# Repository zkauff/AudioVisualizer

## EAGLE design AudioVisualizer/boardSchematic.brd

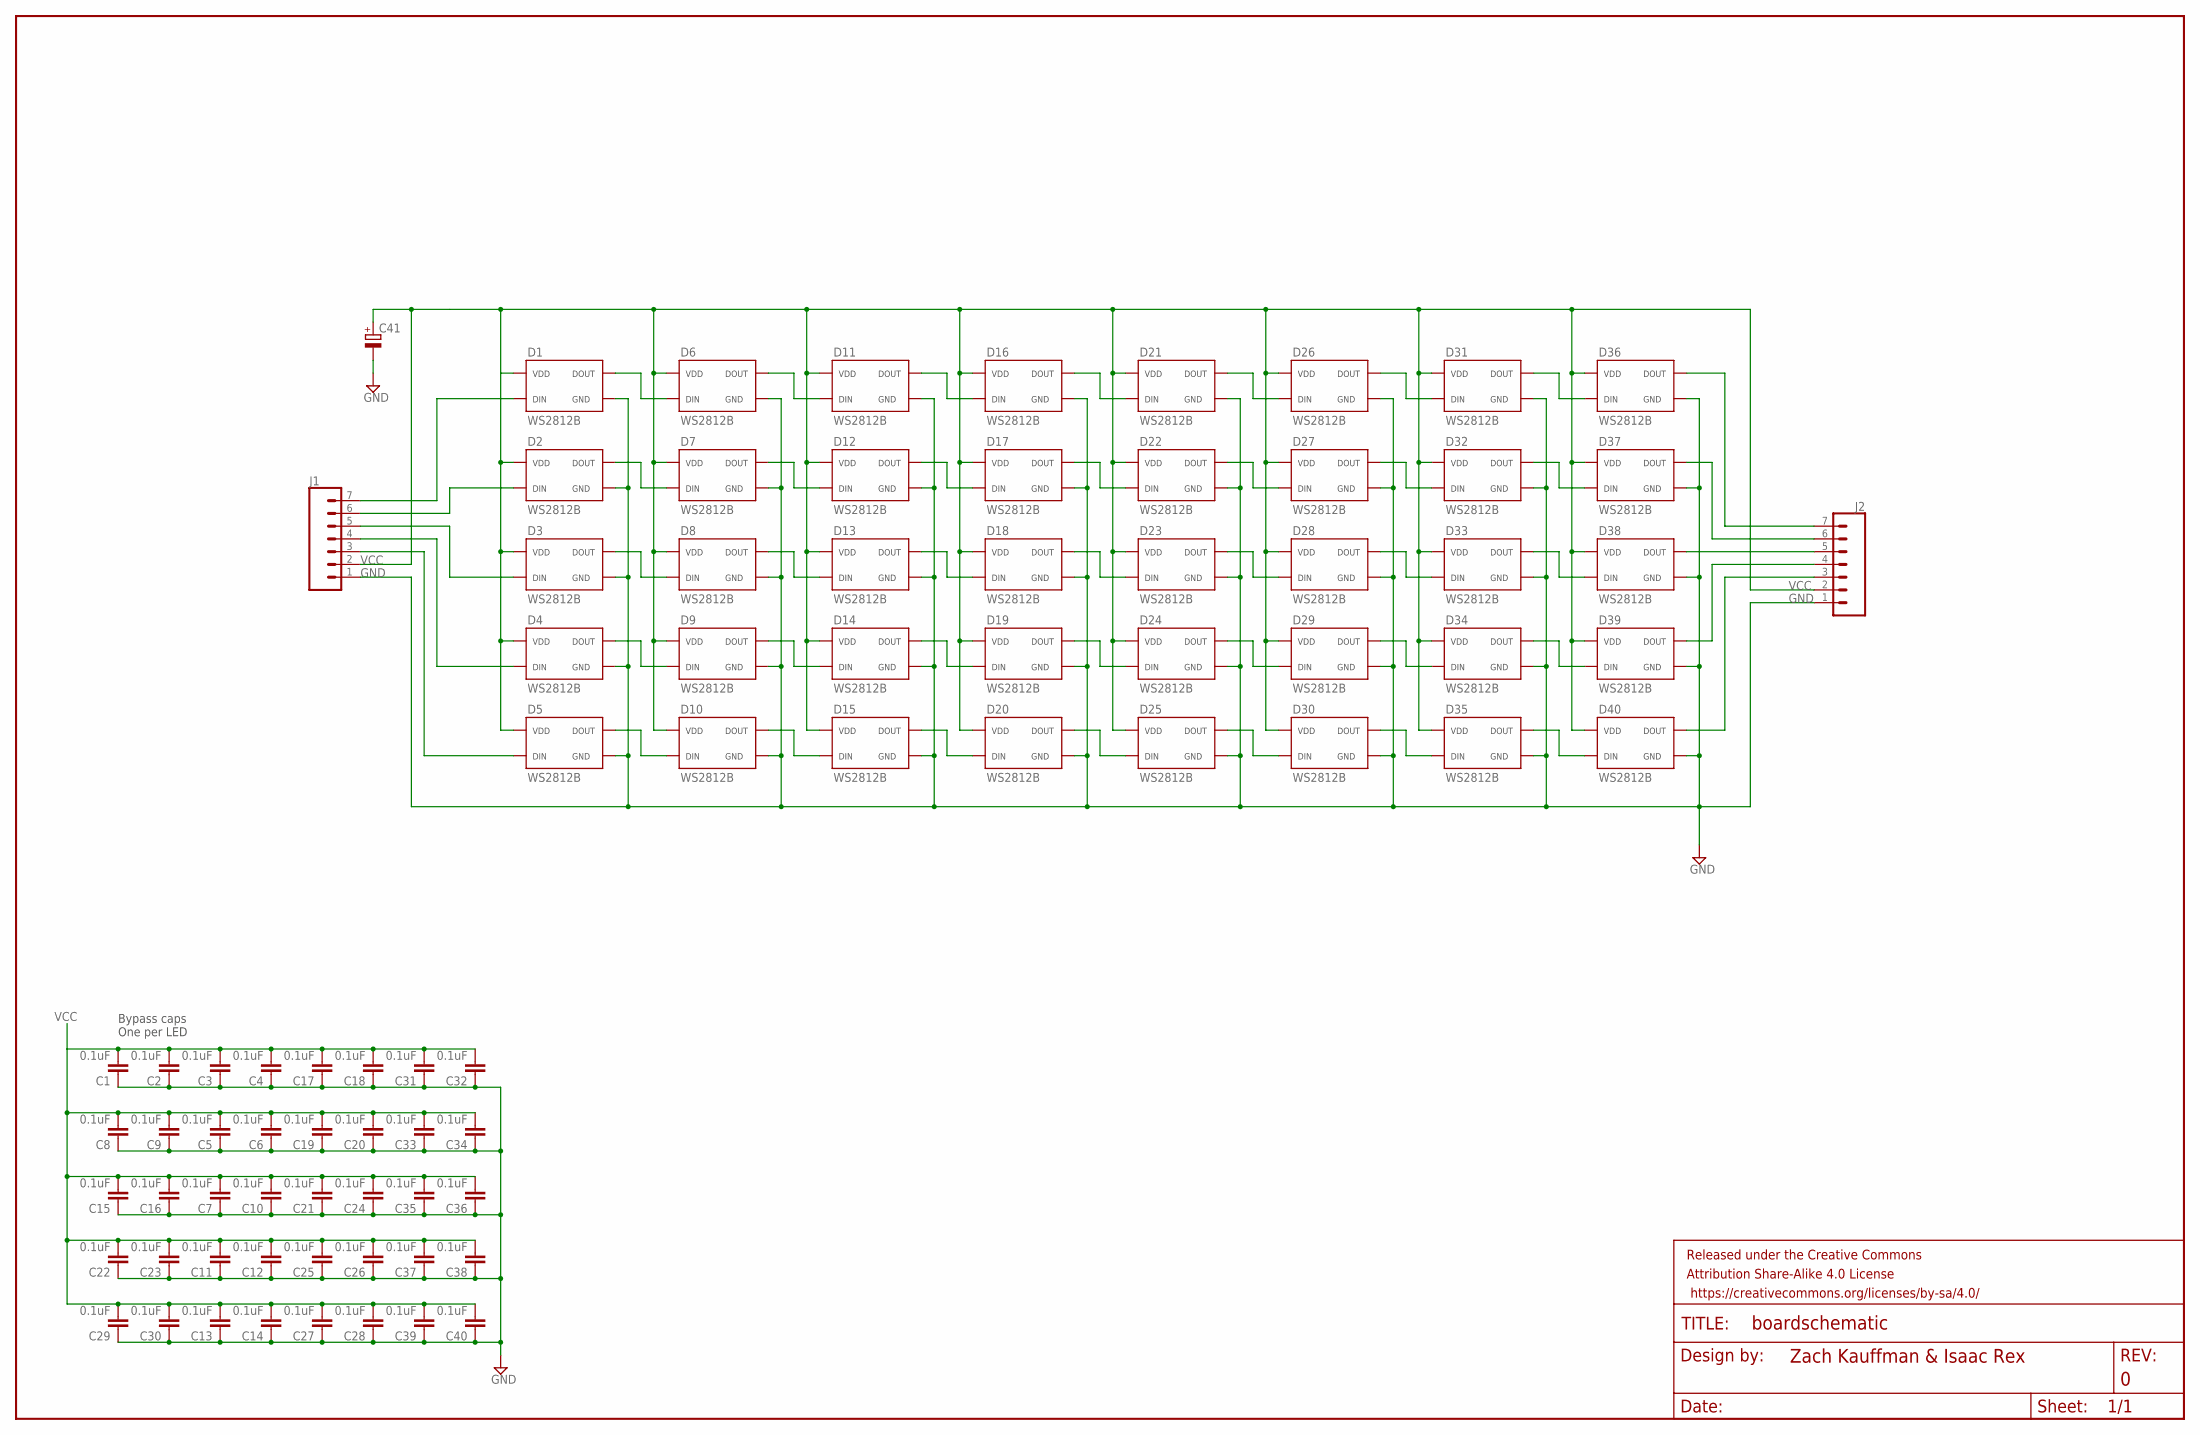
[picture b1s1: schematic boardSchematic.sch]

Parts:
C1, C2, C3, C4, C5, C6, C7, C8, C9, C10, C11, C12, C13, C14, C15, C16, C17, C18, C19, C20, C21, C22, C23, C24, C25, C26, C27, C28, C29, C30, C31, C32, C33, C34, C35, C36, C37, C38, C39, C40: 0.1uF; 0603
C41: CPOL-EUE2-5; E2-5
D1, D2, D3, D4, D5, D6, D7, D8, D9, D10, D11, D12, D13, D14, D15, D16, D17, D18, D19, D20, D21, D22, D23, D24, D25, D26, D27, D28, D29, D30, D31, D32, D33, D34, D35, D36, D37, D38, D39, D40: WS2812B; 5050
FRAME1: FRAME-LEDGER; CREATIVE_COMMONS
J1, J2: CONN_07LOCK_LONGPADS; 1X07_LOCK_LONGPADS

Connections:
GND: C1.1, C2.1, C3.1, C4.1, C5.1, C6.1, C7.1, C8.1, C9.1, C10.1, C11.1, C12.1, C13.1, C14.1, C15.1, C16.1, C17.1, C18.1, C19.1, C20.1, C21.1, C22.1, C23.1, C24.1, C25.1, C26.1, C27.1, C28.1, C29.1, C30.1, C31.1, C32.1, C33.1, C34.1, C35.1, C36.1, C37.1, C38.1, C39.1, C40.1, C41.-, D1.VSS (GND), D2.VSS (GND), D3.VSS (GND), D4.VSS (GND), D5.VSS (GND), D6.VSS (GND), D7.VSS (GND), D8.VSS (GND), D9.VSS (GND), D10.VSS (GND), D11.VSS (GND), D12.VSS (GND), D13.VSS (GND), D14.VSS (GND), D15.VSS (GND), D16.VSS (GND), D17.VSS (GND), D18.VSS (GND), D19.VSS (GND), D20.VSS (GND), D21.VSS (GND), D22.VSS (GND), D23.VSS (GND), D24.VSS (GND), D25.VSS (GND), D26.VSS (GND), D27.VSS (GND), D28.VSS (GND), D29.VSS (GND), D30.VSS (GND), D31.VSS (GND), D32.VSS (GND), D33.VSS (GND), D34.VSS (GND), D35.VSS (GND), D36.VSS (GND), D37.VSS (GND), D38.VSS (GND), D39.VSS (GND), D40.VSS (GND), J1.1, J2.1
unnamed: D5.DOUT, D10.DIN
unnamed: D5.DIN, J1.3
unnamed: D4.DOUT, D9.DIN
unnamed: D1.DOUT, D6.DIN
unnamed: D10.DOUT, D15.DIN
unnamed: D2.DOUT, D7.DIN
unnamed: D3.DOUT, D8.DIN
unnamed: D9.DOUT, D14.DIN
unnamed: D6.DOUT, D11.DIN
unnamed: D7.DOUT, D12.DIN
unnamed: D8.DOUT, D13.DIN
unnamed: D4.DIN, J1.4
unnamed: D15.DOUT, D20.DIN
unnamed: D3.DIN, J1.5
unnamed: D14.DOUT, D19.DIN
unnamed: D11.DOUT, D16.DIN
unnamed: D12.DOUT, D17.DIN
unnamed: D13.DOUT, D18.DIN
unnamed: D2.DIN, J1.6
unnamed: D20.DOUT, D25.DIN
unnamed: D1.DIN, J1.7
unnamed: D19.DOUT, D24.DIN
unnamed: D16.DOUT, D21.DIN
unnamed: D17.DOUT, D22.DIN
unnamed: D18.DOUT, D23.DIN
unnamed: D37.DOUT, J2.6
unnamed: D25.DOUT, D30.DIN
unnamed: D36.DOUT, J2.7
unnamed: D24.DOUT, D29.DIN
unnamed: D21.DOUT, D26.DIN
unnamed: D22.DOUT, D27.DIN
unnamed: D23.DOUT, D28.DIN
unnamed: D38.DOUT, J2.5
unnamed: D30.DOUT, D35.DIN
unnamed: D39.DOUT, J2.4
unnamed: D29.DOUT, D34.DIN
unnamed: D26.DOUT, D31.DIN
unnamed: D27.DOUT, D32.DIN
unnamed: D28.DOUT, D33.DIN
unnamed: D40.DOUT, J2.3
unnamed: D35.DOUT, D40.DIN
unnamed: D34.DOUT, D39.DIN
unnamed: D31.DOUT, D36.DIN
unnamed: D32.DOUT, D37.DIN
unnamed: D33.DOUT, D38.DIN
VCC: C1.2, C2.2, C3.2, C4.2, C5.2, C6.2, C7.2, C8.2, C9.2, C10.2, C11.2, C12.2, C13.2, C14.2, C15.2, C16.2, C17.2, C18.2, C19.2, C20.2, C21.2, C22.2, C23.2, C24.2, C25.2, C26.2, C27.2, C28.2, C29.2, C30.2, C31.2, C32.2, C33.2, C34.2, C35.2, C36.2, C37.2, C38.2, C39.2, C40.2, C41.+, D1.VDD, D2.VDD, D3.VDD, D4.VDD, D5.VDD, D6.VDD, D7.VDD, D8.VDD, D9.VDD, D10.VDD, D11.VDD, D12.VDD, D13.VDD, D14.VDD, D15.VDD, D16.VDD, D17.VDD, D18.VDD, D19.VDD, D20.VDD, D21.VDD, D22.VDD, D23.VDD, D24.VDD, D25.VDD, D26.VDD, D27.VDD, D28.VDD, D29.VDD, D30.VDD, D31.VDD, D32.VDD, D33.VDD, D34.VDD, D35.VDD, D36.VDD, D37.VDD, D38.VDD, D39.VDD, D40.VDD, J1.2, J2.2

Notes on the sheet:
Bypass caps One per LED

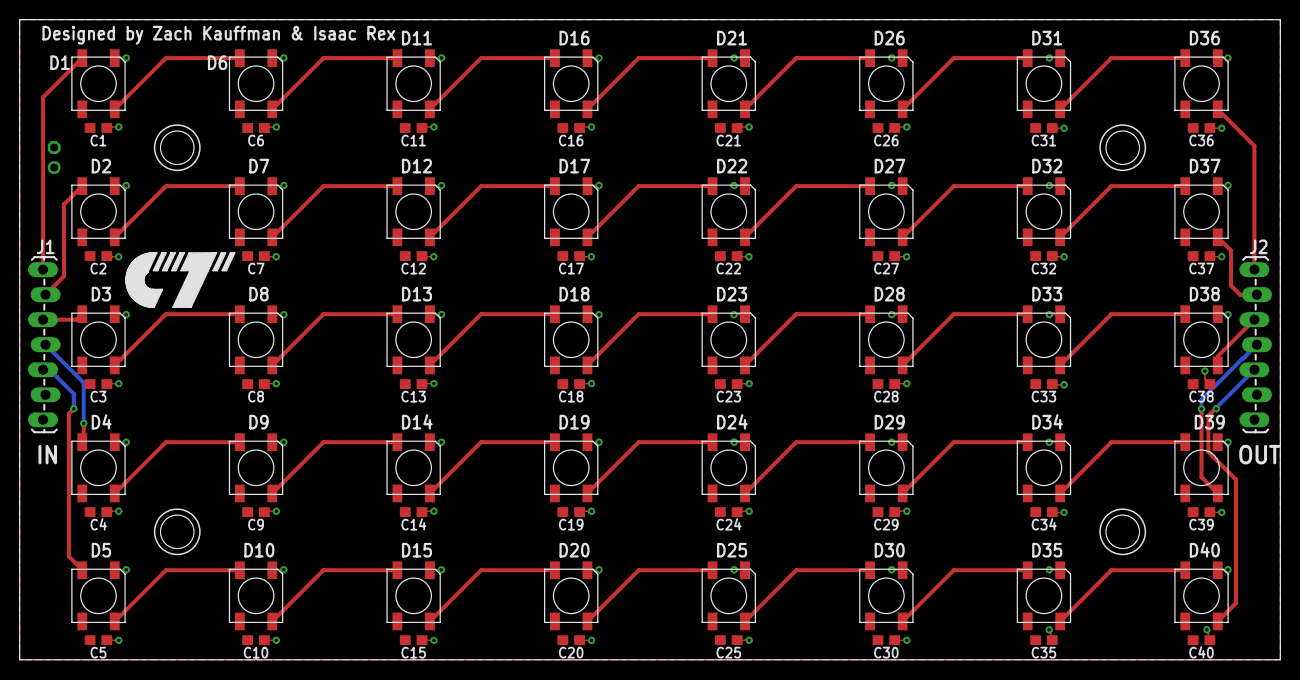
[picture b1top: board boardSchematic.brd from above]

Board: 2 copper layers, 128.0 x 65.0 mm, 84 parts (1 on the bottom side), 47 nets.

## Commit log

2019-02-08 Initial commit.
2019-02-09 Created part in Eagle for the WS2812b
2019-02-23 Worked on board schematic.
2019-02-23 fixed connectors
2019-03-09 started layout
2019-03-17 added scripts to calaculate the x & y posistions for LEDs and Caps. Started aranging elements.
2019-03-30 Finished board layout

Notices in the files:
parts and their libraries:
SparkFun-Capacitors: Licensing: Creative Commons ShareAlike 4.0 International - https://creativecommons.org/licenses/by-sa/4.0
SparkFun-Aesthetics: Released under the Creative Commons Attribution Share-Alike 4.0 License
SparkFun-Aesthetics: https://creativecommons.org/licenses/by-sa/4.0
